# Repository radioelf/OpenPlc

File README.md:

# OpenPlc
Hardware for OpenPLC with raspberry PI Z and Mod. software OpenPlc

# Original code:
https://github.com/thiagoralves/OpenPLC_v3

Creative Commons License Disclaimer

UNLESS OTHERWISE MUTUALLY AGREED TO BY THE PARTIES IN WRITING, LICENSOR OFFERS THE WORK AS-IS AND MAKES NO REPRESENTATIONS OR WARRANTIES OF ANY KIND CONCERNING THE WORK, EXPRESS, IMPLIED, STATUTORY OR OTHERWISE, INCLUDING, WITHOUT LIMITATION, WARRANTIES OF TITLE, MERCHANTIBILITY, FITNESS FOR A PARTICULAR PURPOSE, NONINFRINGEMENT, OR THE ABSENCE OF LATENT OR OTHER DEFECTS, ACCURACY, OR THE PRESENCE OF ABSENCE OF ERRORS, WHETHER OR NOT DISCOVERABLE. SOME JURISDICTIONS DO NOT ALLOW THE EXCLUSION OF IMPLIED WARRANTIES, SO SUCH EXCLUSION MAY NOT APPLY TO YOU. EXCEPT TO THE EXTENT REQUIRED BY APPLICABLE LAW, IN NO EVENT WILL LICENSOR BE LIABLE TO YOU ON ANY LEGAL THEORY FOR ANY SPECIAL, INCIDENTAL, CONSEQUENTIAL, PUNITIVE OR EXEMPLARY DAMAGES ARISING OUT OF THIS LICENSE OR THE USE OF THE WORK, EVEN IF LICENSOR HAS BEEN ADVISED OF THE POSSIBILITY OF SUCH DAMAGES.

http://creativecommons.org/licenses/by-sa/3.0/

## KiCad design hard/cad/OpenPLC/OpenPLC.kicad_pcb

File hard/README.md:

Diseño de PCBs con Kicad para OpenPlc usando como CPU una Raspberry Pi Z (int-out) y Arduino Nano para las PBCs 
de entradas/salidas analógicas

Creative Commons License Disclaimer

UNLESS OTHERWISE MUTUALLY AGREED TO BY THE PARTIES IN WRITING, LICENSOR OFFERS THE WORK AS-IS AND MAKES NO REPRESENTATIONS OR
WARRANTIES OF ANY KIND CONCERNING THE WORK, EXPRESS, IMPLIED, STATUTORY OR OTHERWISE, INCLUDING, WITHOUT LIMITATION, 
WARRANTIES OF TITLE, MERCHANTIBILITY, FITNESS FOR A PARTICULAR PURPOSE, NONINFRINGEMENT, OR THE ABSENCE OF LATENT OR 
OTHER DEFECTS, ACCURACY, OR THE PRESENCE OF ABSENCE OF ERRORS, WHETHER OR NOT DISCOVERABLE. SOME JURISDICTIONS DO NOT 
ALLOW THE EXCLUSION OF IMPLIED WARRANTIES, SO SUCH EXCLUSION MAY NOT APPLY TO YOU. EXCEPT TO THE EXTENT REQUIRED BY 
APPLICABLE LAW, IN NO EVENT WILL LICENSOR BE LIABLE TO YOU ON ANY LEGAL THEORY FOR ANY SPECIAL, INCIDENTAL, CONSEQUENTIAL,
PUNITIVE OR EXEMPLARY DAMAGES ARISING OUT OF THIS LICENSE OR THE USE OF THE WORK, EVEN IF LICENSOR HAS BEEN ADVISED OF 
THE POSSIBILITY OF SUCH DAMAGES.

http://creativecommons.org/licenses/by-sa/3.0/

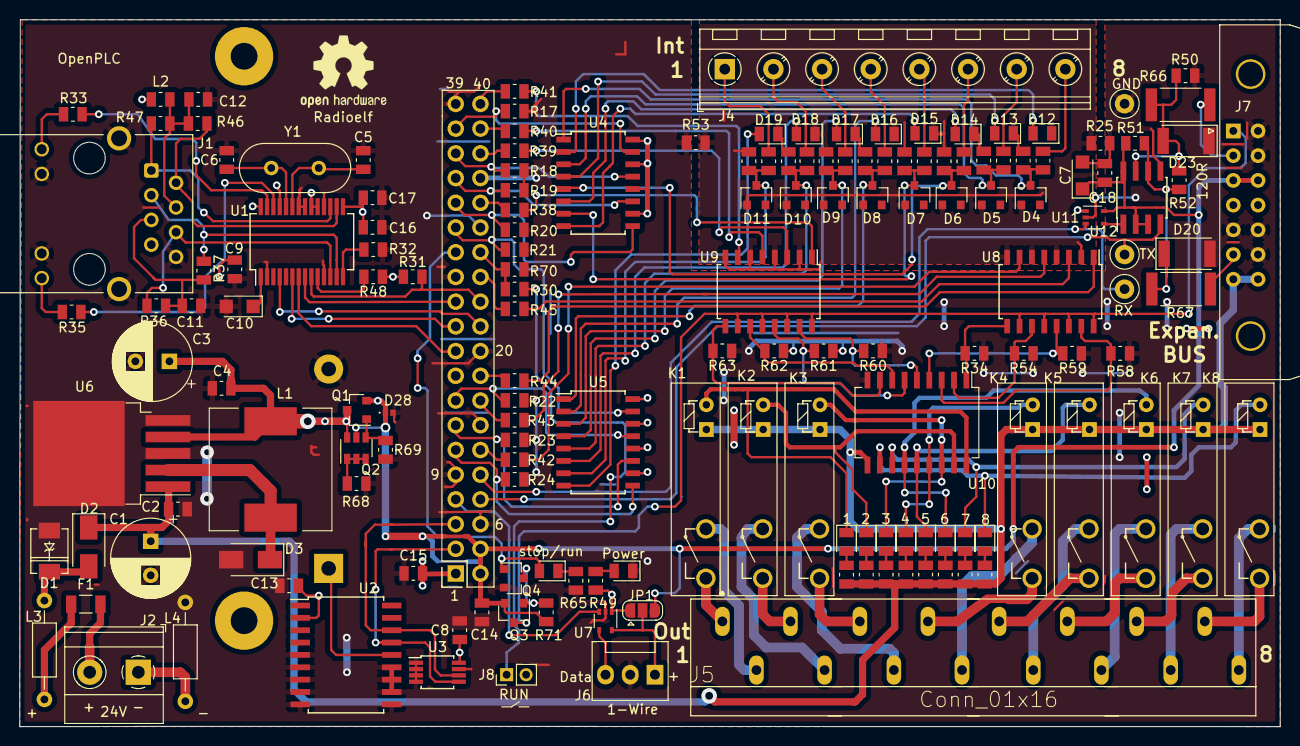
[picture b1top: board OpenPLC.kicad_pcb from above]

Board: 2 copper layers, 129.5 x 72.6 mm, 165 parts (1 on the bottom side), 141 nets.

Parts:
BT1: Battery_Cell; BatteryHolder_Keystone_103_1x20mm
C1: 100uF 50V; CP_Radial_D8.0mm_P3.50mm
C2, C4, C8, C9, C13, C14, C15, C16, C17, C18: 100nF; C_0805_2012Metric
C3: 1000uF; CP_Radial_D8.0mm_P3.50mm
C5, C6: 18pF; C_0805_2012Metric
C7, C10: 10uF; CP_EIA-3216-10_Kemet-I
C11, C12: 10nF; C_0805_2012Metric
D1: SMBJ36A; DO-214AA
D2: STPS1L30A; D_SMA
D3: SS34; D_SMA
D4, D5, D6, D7, D8, D9, D10, D11: RGF1B; D_SOT-23_ANK
D12, D13, D14, D15, D16, D17, D18, D19, D21, D24, D25, D26, D27, D29, D30, D31: LED; LED_0805_2012Metric
D20, D23: 6V8C; D_2010_5025Metric
D22: stop/run; LED_0805_2012Metric
D28: PESD0402-140; D_0402_1005Metric
D32: Power; LED_0805_2012Metric
F1: PPTC- 250mA; Fuse_1206_3216Metric
J1: RJ45-TRANSFO_HR911105A; RJ45_Hanrun_HR911105A
J2: Conn_01x02; TerminalBlock_Phoenix_MKDS-1,5-2_1x02_P5.00mm_Horizontal
J3: Raspberry_Pi_2_3; Raspberry_Pi_Zero_invert
J4: Conn_01x08; TerminalBlock_RND_205-00051_1x08_P5.00mm_Horizontal
J5: Conn_01x16; WAGO_250-204-16
J6: 1-Wire; FanPinHeader_1x03_P2.54mm_Vertical
J7: Conn_02x07_Odd_Even; IDC-Header_2x07_P2.54mm_Horizontal_Lock
J8: On-Off RUN; PinHeader_1x02_P2.00mm_Vertical
JP1: 3.3v-5v; SolderJumper-3_P1.3mm_Open_RoundedPad1.0x1.5mm
K1, K2, K3, K4, K5, K6, K7, K8: APA331; Relay_apan3124
L1: 47uH; L_12x12mm_H6mm
L2: 10uH; L_0805_2012Metric
L3, L4: 10uH; L_Axial_L5.3mm_D2.2mm_P10.16mm_Horizontal_Vishay_IM-1
LOGO1: Logo_Open_Hardware_Large; OSHW-Logo2_9.8x8mm_SilkScreen
Q1, Q3: DMG2305; SOT-23
Q2: DMMT5401; SOT-23-6
Q4: BC847; SOT-23
R1, R2, R3, R4, R5, R6, R7, R8, R26, R27, R28, R29, R55, R56, R57, R64: 4k7; R_0805_2012Metric
R9, R10, R11, R12, R13, R14, R15, R16, R31, R34, R48, R54, R58, R59, R60, R61, R62, R63, R70: 10k; R_0805_2012Metric
R17, R18, R19, R20, R21, R22, R23, R24: 5k1; R_0805_2012Metric
R25, R53: 0R; R_0805_2012Metric
R30, R33, R35, R38, R39, R40, R41, R42, R43, R44, R45, R49, R65: 1k; R_0805_2012Metric
R32: 2k7; R_0805_2012Metric
R36, R37, R46, R47: 50R; R_0805_2012Metric
R50, R51: 4k2; R_0805_2012Metric
R52: 120R; R_0805_2012Metric
R66, R67: 100R; R_2512_6332Metric
R68, R69, R71: 47K; R_0805_2012Metric
TP1: RX; TestPoint_Loop_D1.80mm_Drill1.0mm_Beaded
TP2: TX; TestPoint_Loop_D1.80mm_Drill1.0mm_Beaded
TP3: GND; TestPoint_Loop_D1.80mm_Drill1.0mm_Beaded
U1: ENC28J60x-SS; SSOP-28_5.3x10.2mm_P0.65mm
U2: DS3231MZ; SOIC-18W_7.5x11.6mm_P1.27mm
U3: 24LC32; MSOP-8_3x3mm_P0.65mm
U4, U5, U8, U9: TLP281-4; SOIC-16W_5.3x10.2mm_P1.27mm
U6: LM2596S-5; TO-263-5_TabPin3
U7, U11: MAX3370; SOT-353_SC-70-5
U10: ULN2803A; SOP-18_7.0x12.5mm_P1.27mm
U12: MAX13487; PowerIntegrations_SO-8
Y1: 25Mhz; Crystal_HC49-4H_Vertical

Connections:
+3V3: C8.2, C9.2, C13.1, C15.2, C16.1, C17.2, J3.1, J3.17, J7.7, J7.8, J8.2, JP1.1, L2.1, R31.2, R48.1, R49.1, U1.15, U1.19, U1.20, U1.25, U1.28, U2.2, U3.8, U4.10, U4.12, U4.14, U4.16, U5.10, U5.12, U5.14, U5.16, U7.1, U11.1
+5V: C7.1, C14.2, C18.2, D28.1, J3.2, J3.4, J7.5, J7.6, JP1.3, Q1.2, Q2.5, Q3.2, R51.2, R71.1, U11.5, U12.2, U12.3, U12.8
+24V: C1.1, C2.1, D2.1, J7.13, J7.14, K1.3, K2.3, K3.3, K4.3, K5.3, K6.3, K7.3, K8.3, R26.1, R27.1, R28.1, R29.1, R55.1, R56.1, R57.1, R64.1, U6.1, U10.10
/%IX0.0: J3.11, R24.1, U5.9
/%IX0.1: J3.13, R23.1, U5.11
/%IX0.2: J3.15, R22.1, U5.13
/%IX0.3: J3.29, R21.1, U5.15
/%IX0.4: J3.31, R20.1, U4.9
/%IX0.5: J3.33, R19.1, U4.11
/%IX0.6: J3.35, R18.1, U4.13
/%IX0.7: J3.37, R17.1, U4.15
/%QV0.7: J3.40, R41.2
/%QX0.0: J3.12, R42.2
/%QX0.1: J3.16, R43.2
/%QX0.2: J3.18, R44.2
/%QX0.3: J3.26, R45.2
/%QX0.4: J3.32, R38.2
/%QX0.5: J3.36, R39.2
/%QX0.6: J3.38, R40.2
/Bus/A-RS485: J7.11, R67.1
/Bus/B-RS485: J7.3, R66.1
/CLK: J3.23, U1.8
/EtherCAT/Reset: R48.2, U1.10
/MISO: J3.21, U1.6
/MOSI: J3.19, U1.7
/RPI-Zero/1-Wire: J3.7, U7.3
/RPI-Zero/LED: D22.2, J3.27, Q4.1
/RPI-Zero/On-Off: J8.1, R30.1
/RPI-Zero/RUN: J3.28, R30.2, R70.2
/RUN-STOP: J7.1, Q3.3, U8.10, U8.12, U8.14, U8.16, U9.10, U9.12, U9.14, U9.16
/RXD: J3.10, TP1.1, U11.3
/SDA: J3.3, U2.15, U3.5
/SDL: J3.5, U2.16, U3.6
/TXD: J3.8, TP2.1, U12.4
/outputs/Out1A: J5.1, K1.2
/outputs/Out1B: J5.2, K1.1
/outputs/Out2A: J5.3, K2.2
/outputs/Out2B: J5.4, K2.1
/outputs/Out3A: J5.5, K3.2
/outputs/Out3B: J5.6, K3.1
/outputs/Out4A: J5.7, K4.2
/outputs/Out4B: J5.8, K4.1
/outputs/Out5A: J5.9, K5.2
/outputs/Out5B: J5.10, K5.1
/outputs/Out6A: J5.11, K6.2
/outputs/Out6B: J5.12, K6.1
/outputs/Out7A: J5.13, K7.2
/outputs/Out7B: J5.14, K7.1
/outputs/Out8A: J5.15, K8.2
/outputs/Out8B: J5.16, K8.1
/~CS: J3.24, R31.1, U1.9
/~INT: J3.22, U1.4
GND: BT1.2, C1.2, C2.2, C3.2, C4.2, C5.2, C6.1, C7.2, C8.1, C9.1, C10.2, C11.1, C12.1, C13.2, C14.1, C15.1, C16.2, C17.1, C18.1, D1.2, D3.2, D20.2, D23.1, D28.2, D32.1, J1.8, J1.10, J1.11, J1.SH, J3.6, J3.9, J3.14, J3.20, J3.25, J3.30, J3.34, J3.39, J6.2, J7.2, J7.4, J7.9, J7.10, J7.12, L4.1, Q4.2, R17.2, R18.2, R19.2, R20.2, R21.2, R22.2, R23.2, R24.2, R25.1, R32.2, R34.1, R50.1, R53.1, R54.1, R58.1, R59.1, R60.1, R61.1, R62.1, R63.1, R65.2, R68.2, R69.2, R70.1, TP3.1, U1.2, U1.11, U1.18, U1.21, U1.22, U2.5, U2.6, U2.7, U2.8, U2.9, U2.10, U2.11, U2.12, U2.13, U3.1, U3.2, U3.3, U3.4, U3.7, U6.3, U6.5, U7.2, U10.9, U11.2, U12.5
GNDREF: D4.2, D5.2, D6.2, D7.2, D8.2, D9.2, D10.2, D11.2, D12.1, D13.1, D14.1, D15.1, D16.1, D17.1, D18.1, D19.1, R9.2, R10.2, R11.2, R12.2, R13.2, R14.2, R15.2, R16.2, R25.2, R53.2, U8.2, U8.4, U8.6, U8.8, U9.2, U9.4, U9.6, U9.8
unnamed: BT1.1, U2.14
unnamed: C3.1, C4.1, L1.2, Q1.3, Q2.6, U6.4
unnamed: C5.1, U1.23, Y1.1
unnamed: C6.2, U1.24, Y1.2
unnamed: C10.1, U1.1
unnamed: C11.2, J1.5, R36.1, R37.1
unnamed: C12.2, J1.4, L2.2, R46.1, R47.1
unnamed: D1.1, D2.2, L3.2
unnamed: D3.1, L1.1, U6.2
unnamed: D4.1, R1.1, R11.1, U4.1
unnamed: D5.1, R2.1, R12.1, U4.3
unnamed: D6.1, R3.1, R13.1, U4.5
unnamed: D7.1, R4.1, R14.1, U4.7
unnamed: D8.1, R5.1, R15.1, U5.1
unnamed: D9.1, R6.1, R16.1, U5.3
unnamed: D10.1, R7.1, R9.1, U5.5
unnamed: D11.1, R8.1, R10.1, U5.7
unnamed: D12.2, U4.2
unnamed: D13.2, U4.4
unnamed: D14.2, U4.6
unnamed: D15.2, U4.8
unnamed: D16.2, U5.2
unnamed: D17.2, U5.4
unnamed: D18.2, U5.6
unnamed: D19.2, U5.8
unnamed: D20.1, R51.1, R52.1, R67.2, U12.6
unnamed: D21.1, K1.4, U10.18
unnamed: D21.2, R64.2
unnamed: D22.1, R65.1
unnamed: D23.2, R50.2, R52.2, R66.2, U12.7
unnamed: D24.1, K6.4, U10.13
unnamed: D24.2, R26.2
unnamed: D25.1, K5.4, U10.14
unnamed: D25.2, R27.2
unnamed: D26.1, K8.4, U10.11
unnamed: D26.2, R28.2
unnamed: D27.1, K7.4, U10.12
unnamed: D27.2, R29.2
unnamed: D29.1, K2.4, U10.17
unnamed: D29.2, R55.2
unnamed: D30.1, K3.4, U10.16
unnamed: D30.2, R56.2
unnamed: D31.1, K4.4, U10.15
unnamed: D31.2, R57.2
unnamed: D32.2, R49.2
unnamed: F1.1, L3.1
unnamed: F1.2, J2.2
unnamed: J1.1, R47.2, U1.17
unnamed: J1.2, R46.2, U1.16
unnamed: J1.3, R37.2, U1.13
unnamed: J1.6, R36.2, U1.12
unnamed: J1.9, R33.1
unnamed: J1.12, R35.1
unnamed: J2.1, L4.2
unnamed: J4.1, R8.2
unnamed: J4.2, R7.2
unnamed: J4.3, R6.2
unnamed: J4.4, R5.2
unnamed: J4.5, R4.2
unnamed: J4.6, R3.2
unnamed: J4.7, R2.2
unnamed: J4.8, R1.2
unnamed: J6.1, JP1.2, U7.5
unnamed: J6.3, U7.4
unnamed: Q1.1, Q2.4, R69.1
unnamed: Q2.1, Q2.2, Q2.3, R68.1
unnamed: Q3.1, Q4.3, R71.2
unnamed: R32.1, U1.14
unnamed: R33.2, U1.27
unnamed: R34.2, U8.9, U10.1
unnamed: R35.2, U1.26
unnamed: R38.1, U9.1
unnamed: R39.1, U9.3
unnamed: R40.1, U9.5
unnamed: R41.1, U9.7
unnamed: R42.1, U8.7
unnamed: R43.1, U8.5
unnamed: R44.1, U8.1
unnamed: R45.1, U8.3
unnamed: R54.2, U8.11, U10.2
unnamed: R58.2, U8.15, U10.3
unnamed: R59.2, U8.13, U10.4
unnamed: R60.2, U9.15, U10.5
unnamed: R61.2, U9.13, U10.6
unnamed: R62.2, U9.11, U10.7
unnamed: R63.2, U9.9, U10.8
unnamed: U11.4, U12.1

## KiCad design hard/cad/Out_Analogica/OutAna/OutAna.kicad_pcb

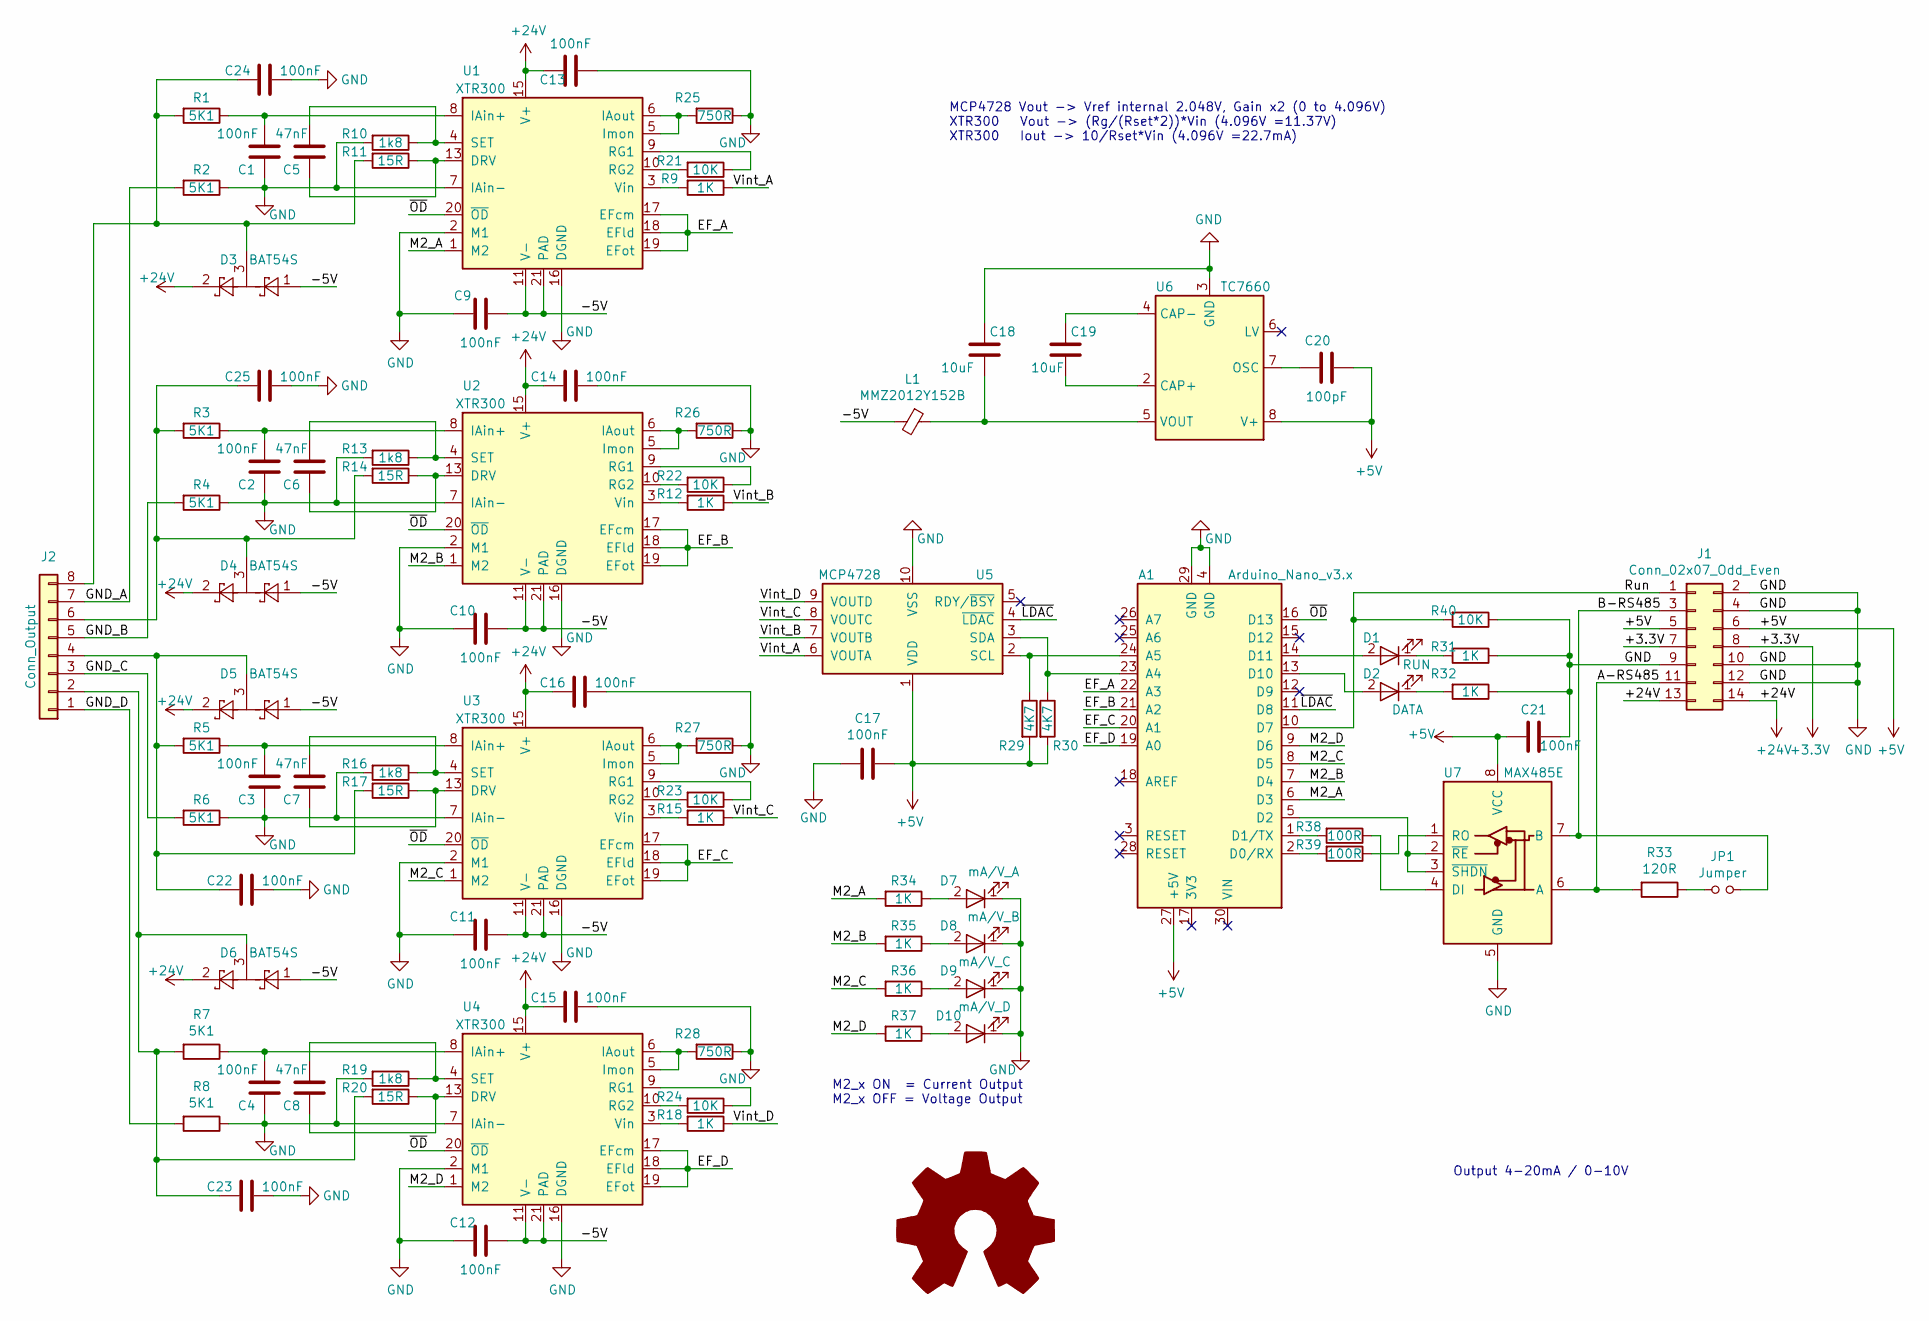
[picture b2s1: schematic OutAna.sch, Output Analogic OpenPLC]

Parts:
A1: Arduino_Nano_v3.x; Arduino_Nano
C1, C2, C3, C4, C9, C10, C11, C12, C13, C14, C15, C16, C17, C21, C22, C23, C24, C25: 100nF; C_0805_2012Metric
C5, C6, C7, C8: 47nF; C_0805_2012Metric
C18, C19: 10uF; C_0805_2012Metric
C20: 100pF; C_0805_2012Metric
D1: RUN; LED_0603_1608Metric
D2: DATA; LED_0603_1608Metric
D3, D4, D5, D6: BAT54S; SOT-23
D7: mA/V_A; LED_0603_1608Metric
D8: mA/V_B; LED_0603_1608Metric
D9: mA/V_C; LED_0603_1608Metric
D10: mA/V_D; LED_0603_1608Metric
J1: Conn_02x07_Odd_Even; IDC-Header_2x07_P2.54mm_Vertical
J2: Conn_Output; PhoenixContact_MCV_1,5_8-G-3.5_1x08_P3.50mm_Vertical
JP1: Jumper; SolderJumper-2_P1.3mm_Open_RoundedPad1.0x1.5mm
L1: MMZ2012Y152B; L_0805_2012Metric
LOGO1: Logo_Open_Hardware_Large; OSHW-Logo2_9.8x8mm_SilkScreen
R1, R2, R3, R4, R5, R6, R7, R8: 5K1; R_0805_2012Metric
R9, R12, R15, R18, R31, R32, R34, R35, R36, R37: 1K; R_0805_2012Metric
R10, R13, R16, R19: 1k8; R_0805_2012Metric
R11, R14, R17, R20: 15R; R_0805_2012Metric
R21, R22, R23, R24, R40: 10K; R_0805_2012Metric
R25, R26, R27, R28: 750R; R_0805_2012Metric
R29, R30: 4K7; R_0805_2012Metric
R33: 120R; R_0805_2012Metric
R38, R39: 100R; R_0805_2012Metric
U1, U2, U3, U4: XTR300; QFN-20-1EP_5x5mm_P0.65mm_EP3.35x3.35mm
U5: MCP4728; MSOP-10_3x3mm_P0.5mm
U6: TC7660; SOIC-8_3.9x4.9mm_P1.27mm
U7: MAX485E; PowerIntegrations_SO-8

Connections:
+3V3: J1.7, J1.8
+5V: A1.27 (+5V), C17.1, C20.2, C21.2, J1.5, J1.6, R29.2, R30.2, U5.1 (VDD), U6.8 (V+), U7.8 (VCC)
+24V: C13.1, C14.1, C15.1, C16.1, D3.2, D4.2, D5.2, D6.2, J1.13, J1.14, U1.15 (V+), U2.15 (V+), U3.15 (V+), U4.15 (V+)
/-5V: C9.2, C10.2, C11.2, C12.2, D3.1, D4.1, D5.1, D6.1, L1.2, U1.11 (V-), U1.21 (PAD), U2.11 (V-), U2.21 (PAD), U3.11 (V-), U3.21 (PAD), U4.11 (V-), U4.21 (PAD)
/A-RS485: J1.11, R33.2, U7.6 (A)
/B-RS485: J1.3, JP1.2, U7.7 (B)
/EF_A: A1.22 (A3), U1.17 (EFcm), U1.18 (EFld), U1.19 (EFot)
/EF_B: A1.21 (A2), U2.17 (EFcm), U2.18 (EFld), U2.19 (EFot)
/EF_C: A1.20 (A1), U3.17 (EFcm), U3.18 (EFld), U3.19 (EFot)
/EF_D: A1.19 (A0), U4.17 (EFcm), U4.18 (EFld), U4.19 (EFot)
/GND_A: J2.7, R2.2
/GND_B: J2.5, R4.2
/GND_C: J2.3, R6.2
/GND_D: J2.1, R8.2
/M2_A: A1.6 (D3), R34.2, U1.1 (M2)
/M2_B: A1.7 (D4), R35.2, U2.1 (M2)
/M2_C: A1.8 (D5), R36.2, U3.1 (M2)
/M2_D: A1.9 (D6), R37.2, U4.1 (M2)
/Run: A1.10 (D7), J1.1, R40.2
/Vint_A: R9.1, U5.6 (VOUTA)
/Vint_B: R12.1, U5.7 (VOUTB)
/Vint_C: R15.1, U5.8 (VOUTC)
/Vint_D: R18.1, U5.9 (VOUTD)
/~LDAC: A1.11 (D8), U5.4 (~LDAC)
/~OD: A1.16 (D13), U1.20 (~OD), U2.20 (~OD), U3.20 (~OD), U4.20 (~OD)
GND: A1.4 (GND), A1.29 (GND), C1.2, C2.2, C3.2, C4.2, C9.1, C10.1, C11.1, C12.1, C13.2, C14.2, C15.2, C16.2, C17.2, C18.1, C21.1, C22.2, C23.2, C24.2, C25.2, D7.1 (K), D8.1 (K), D9.1 (K), D10.1 (K), J1.2, J1.4, J1.9, J1.10, J1.12, R2.1, R4.1, R6.1, R8.1, R10.2, R13.2, R16.2, R19.2, R25.1, R26.1, R27.1, R28.1, R31.1, R32.1, R40.1, U1.2 (M1), U1.7 (IAin-), U1.16 (DGND), U2.2 (M1), U2.7 (IAin-), U2.16 (DGND), U3.2 (M1), U3.7 (IAin-), U3.16 (DGND), U4.2 (M1), U4.7 (IAin-), U4.16 (DGND), U5.10 (VSS), U6.3 (GND), U7.5 (GND)
unnamed: A1.1 (D1/TX), R38.2
unnamed: A1.2 (D0/RX), R39.2
unnamed: A1.5 (D2), U7.2 (~RE), U7.3 (~SHDN)
unnamed: A1.13 (D10), D2.2 (A)
unnamed: A1.14 (D11), D1.2 (A)
unnamed: A1.23 (A4), R30.1, U5.3 (SDA)
unnamed: A1.24 (A5), R29.1, U5.2 (SCL)
unnamed: C1.1, R1.1, U1.8 (IAin+)
unnamed: C2.1, R3.1, U2.8 (IAin+)
unnamed: C3.1, R5.1, U3.8 (IAin+)
unnamed: C4.1, R7.1, U4.8 (IAin+)
unnamed: C5.1, R10.1, U1.4 (SET)
unnamed: C5.2, R11.1, U1.13 (DRV)
unnamed: C6.1, R13.1, U2.4 (SET)
unnamed: C6.2, R14.1, U2.13 (DRV)
unnamed: C7.1, R16.1, U3.4 (SET)
unnamed: C7.2, R17.1, U3.13 (DRV)
unnamed: C8.1, R19.1, U4.4 (SET)
unnamed: C8.2, R20.1, U4.13 (DRV)
unnamed: C18.2, L1.1, U6.5 (VOUT)
unnamed: C19.1, U6.4 (CAP-)
unnamed: C19.2, U6.2 (CAP+)
unnamed: C20.1, U6.7 (OSC)
unnamed: C22.1, D5.3, J2.4, R5.2, R17.2
unnamed: C23.1, D6.3, J2.2, R7.2, R20.2
unnamed: C24.1, D3.3, J2.8, R1.2, R11.2
unnamed: C25.1, D4.3, J2.6, R3.2, R14.2
unnamed: D1.1 (K), R31.2
unnamed: D2.1 (K), R32.2
unnamed: D7.2 (A), R34.1
unnamed: D8.2 (A), R35.1
unnamed: D9.2 (A), R36.1
unnamed: D10.2 (A), R37.1
unnamed: JP1.1, R33.1
unnamed: R9.2, U1.3 (Vin)
unnamed: R12.2, U2.3 (Vin)
unnamed: R15.2, U3.3 (Vin)
unnamed: R18.2, U4.3 (Vin)
unnamed: R21.1, U1.9 (RG1)
unnamed: R21.2, U1.10 (RG2)
unnamed: R22.1, U2.9 (RG1)
unnamed: R22.2, U2.10 (RG2)
unnamed: R23.1, U3.9 (RG1)
unnamed: R23.2, U3.10 (RG2)
unnamed: R24.1, U4.9 (RG1)
unnamed: R24.2, U4.10 (RG2)
unnamed: R25.2, U1.5 (Imon), U1.6 (IAout)
unnamed: R26.2, U2.5 (Imon), U2.6 (IAout)
unnamed: R27.2, U3.5 (Imon), U3.6 (IAout)
unnamed: R28.2, U4.5 (Imon), U4.6 (IAout)
unnamed: R38.1, U7.4 (DI)
unnamed: R39.1, U7.1 (RO)

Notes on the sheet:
Output 4-20mA / 0-10V
M2_x ON = Current Output M2_x OFF = Voltage Output
MCP4728 Vout -> Vref internal 2.048V, Gain x2 (0 to 4.096V) XTR300 Vout -> (Rg/(Rset*2))*Vin (4.096V =11.37V) XTR300 Iout -> 10/Rset*Vin (4.096V =22.7mA)

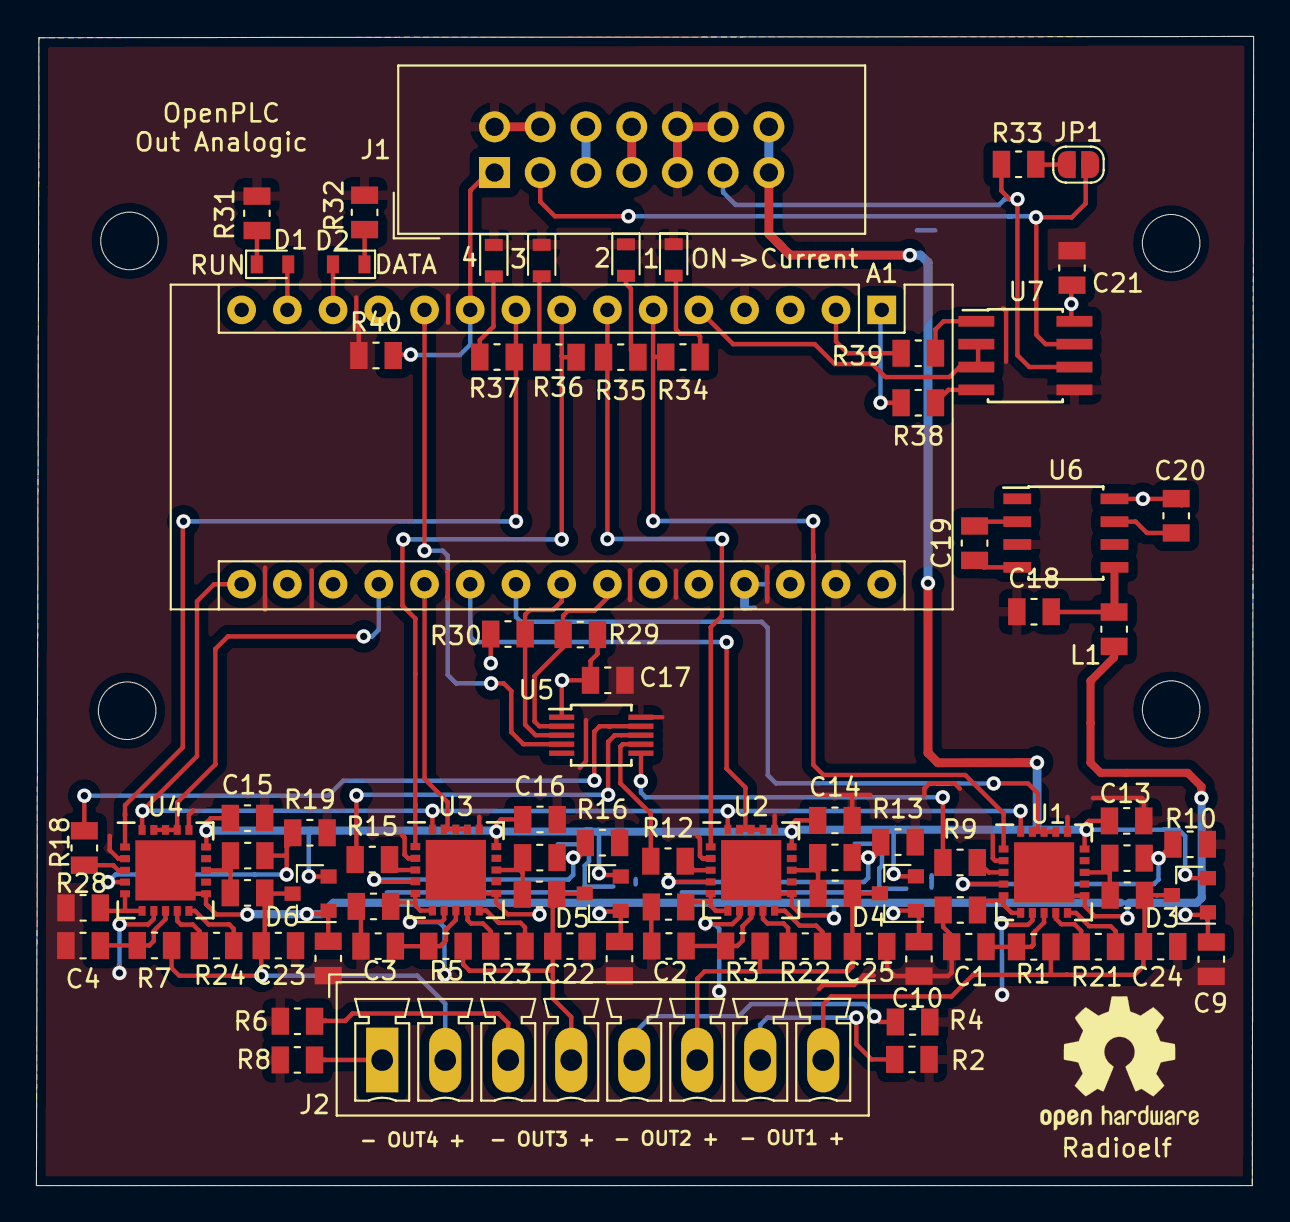
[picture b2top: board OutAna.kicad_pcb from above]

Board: 2 copper layers, 67.6 x 63.8 mm, 88 parts (0 on the bottom side), 78 nets.

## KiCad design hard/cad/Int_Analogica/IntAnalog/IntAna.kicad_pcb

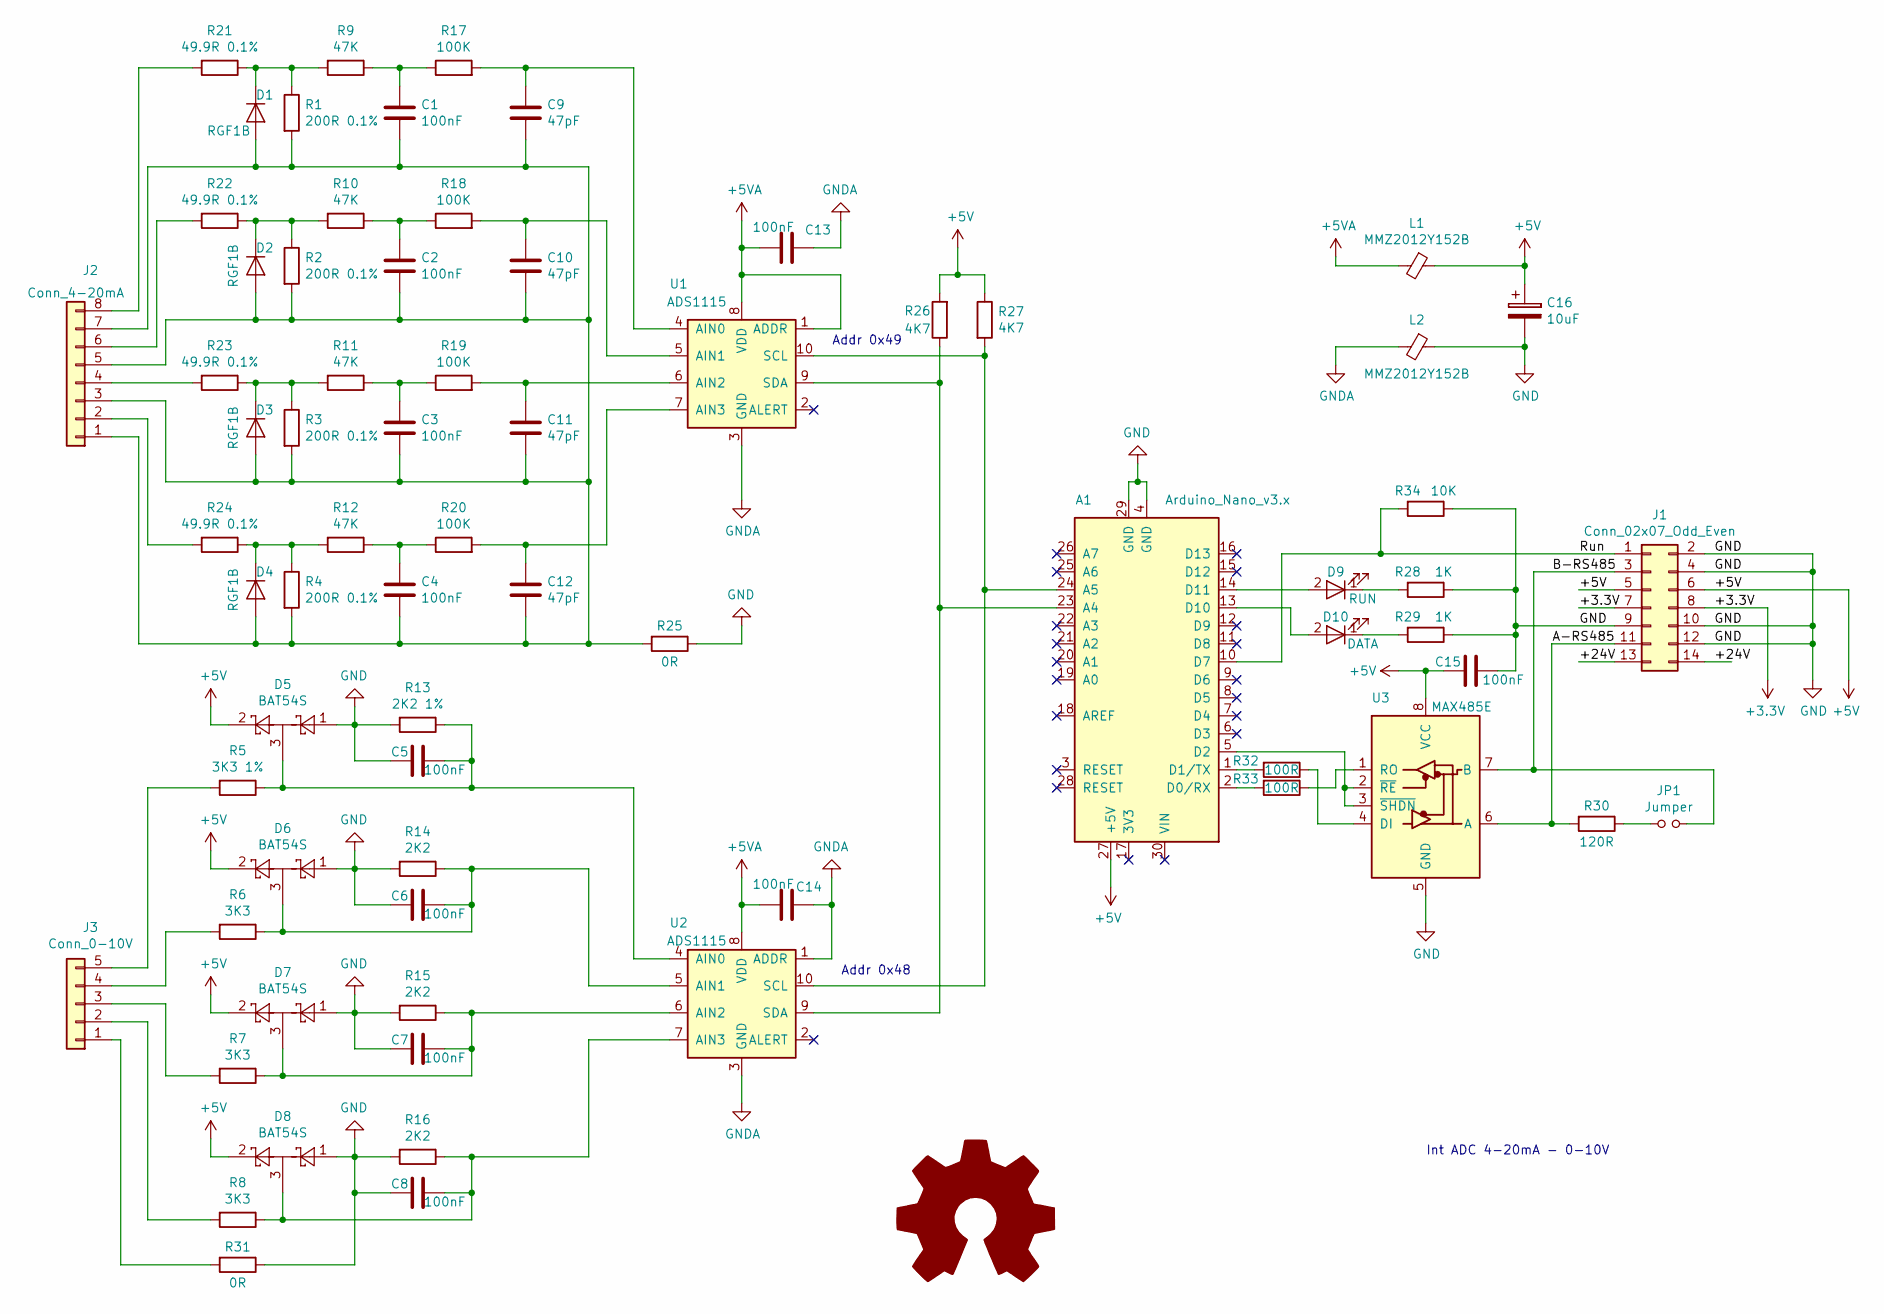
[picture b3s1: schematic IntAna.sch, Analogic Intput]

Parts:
A1: Arduino_Nano_v3.x; Arduino_Nano
C1, C2, C3, C4, C5, C6, C7, C8, C13, C14, C15: 100nF; C_0805_2012Metric
C9, C10, C11, C12: 47pF; C_0805_2012Metric
C16: 10uF; CP_EIA-6032-28_Kemet-C
D1, D2, D3, D4: RGF1B; D_SOT-23_ANK
D5, D6, D7, D8: BAT54S; SOT-23
D9: RUN; LED_0805_2012Metric
D10: DATA; LED_0805_2012Metric
J1: Conn_02x07_Odd_Even; IDC-Header_2x07_P2.54mm_Vertical
J2: Conn_4-20mA; PhoenixContact_MCV_1,5_8-G-3.5_1x08_P3.50mm_Vertical
J3: Conn_0-10V; PhoenixContact_MCV_1,5_5-G-3.5_1x05_P3.50mm_Vertical
JP1: Jumper; SolderJumper-2_P1.3mm_Open_RoundedPad1.0x1.5mm
L1, L2: MMZ2012Y152B; R_0805_2012Metric
LOGO1: Logo_Open_Hardware_Large; OSHW-Logo2_9.8x8mm_SilkScreen
R1, R2, R3, R4: 200R 0.1%; R_0805_2012Metric
R5: 3K3 1%; R_0805_2012Metric
R6, R7, R8: 3K3; R_0805_2012Metric
R9, R10, R11, R12: 47K; R_0805_2012Metric
R13: 2K2 1%; R_0805_2012Metric
R14, R15, R16: 2K2; R_0805_2012Metric
R17, R18, R19, R20: 100K; R_0805_2012Metric
R21, R22, R23, R24: 49.9R 0.1%; R_0805_2012Metric
R25, R31: 0R; R_0805_2012Metric
R26, R27: 4K7; R_0805_2012Metric
R28, R29: 1K; R_0805_2012Metric
R30: 120R; R_0805_2012Metric
R32, R33: 100R; R_0805_2012Metric
R34: 10K; R_0805_2012Metric
U1, U2: ADS1115; TSSOP-10_3x3mm_P0.5mm
U3: MAX485E; PowerIntegrations_SO-8

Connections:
+3V3: J1.7, J1.8
+5V: A1.27 (+5V), C15.1, C16.1, D5.2, D6.2, D7.2, D8.2, J1.5, J1.6, L1.1, R26.2, R27.1, U3.8 (VCC)
+5VA: C13.1, C14.1, L1.2, U1.1 (ADDR), U1.8 (VDD), U2.8 (VDD)
/+24V: J1.13, J1.14
/A-RS485: J1.11, R30.2, U3.6 (A)
/B-RS485: J1.3, JP1.2, U3.7 (B)
/Run: A1.10 (D7), J1.1, R34.2
GND: A1.4 (GND), A1.29 (GND), C5.2, C6.2, C7.2, C8.2, C15.2, C16.2, D5.1, D6.1, D7.1, D8.1, J1.2, J1.4, J1.9, J1.10, J1.12, L2.1, R13.2, R14.2, R15.2, R16.2, R25.1, R28.1, R29.1, R31.1, R34.1, U3.5 (GND)
GNDA: C13.2, C14.2, L2.2, U1.3 (GND), U2.1 (ADDR), U2.3 (GND)
unnamed: A1.1 (D1/TX), R32.2
unnamed: A1.2 (D0/RX), R33.2
unnamed: A1.5 (D2), U3.2 (~RE), U3.3 (~SHDN)
unnamed: A1.13 (D10), D10.2 (A)
unnamed: A1.14 (D11), D9.2 (A)
unnamed: A1.23 (A4), R26.1, U1.9 (SDA), U2.9 (SDA)
unnamed: A1.24 (A5), R27.2, U1.10 (SCL), U2.10 (SCL)
unnamed: C1.1, R9.1, R17.1
unnamed: C1.2, C2.2, C3.2, C4.2, C9.2, C10.2, C11.2, C12.2, D1.2 (A), D2.2 (A), D3.2 (A), D4.2 (A), J2.1, J2.3, J2.5, J2.7, R1.2, R2.2, R3.2, R4.2, R25.2
unnamed: C2.1, R10.1, R18.1
unnamed: C3.1, R11.1, R19.1
unnamed: C4.1, R12.1, R20.1
unnamed: C5.1, D5.3, R5.1, R13.1, U2.4 (AIN0)
unnamed: C6.1, D6.3, R6.1, R14.1, U2.5 (AIN1)
unnamed: C7.1, D7.3, R7.1, R15.1, U2.6 (AIN2)
unnamed: C8.1, D8.3, R8.1, R16.1, U2.7 (AIN3)
unnamed: C9.1, R17.2, U1.4 (AIN0)
unnamed: C10.1, R18.2, U1.5 (AIN1)
unnamed: C11.1, R19.2, U1.6 (AIN2)
unnamed: C12.1, R20.2, U1.7 (AIN3)
unnamed: D1.1 (K), R1.1, R9.2, R21.1
unnamed: D2.1 (K), R2.1, R10.2, R22.1
unnamed: D3.1 (K), R3.1, R11.2, R23.1
unnamed: D4.1 (K), R4.1, R12.2, R24.1
unnamed: D9.1 (K), R28.2
unnamed: D10.1 (K), R29.2
unnamed: J2.2, R24.2
unnamed: J2.4, R23.2
unnamed: J2.6, R22.2
unnamed: J2.8, R21.2
unnamed: J3.1, R31.2
unnamed: J3.2, R8.2
unnamed: J3.3, R7.2
unnamed: J3.4, R6.2
unnamed: J3.5, R5.2
unnamed: JP1.1, R30.1
unnamed: R32.1, U3.4 (DI)
unnamed: R33.1, U3.1 (RO)

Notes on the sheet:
Int ADC 4-20mA - 0-10V
Addr 0x49
Addr 0x48

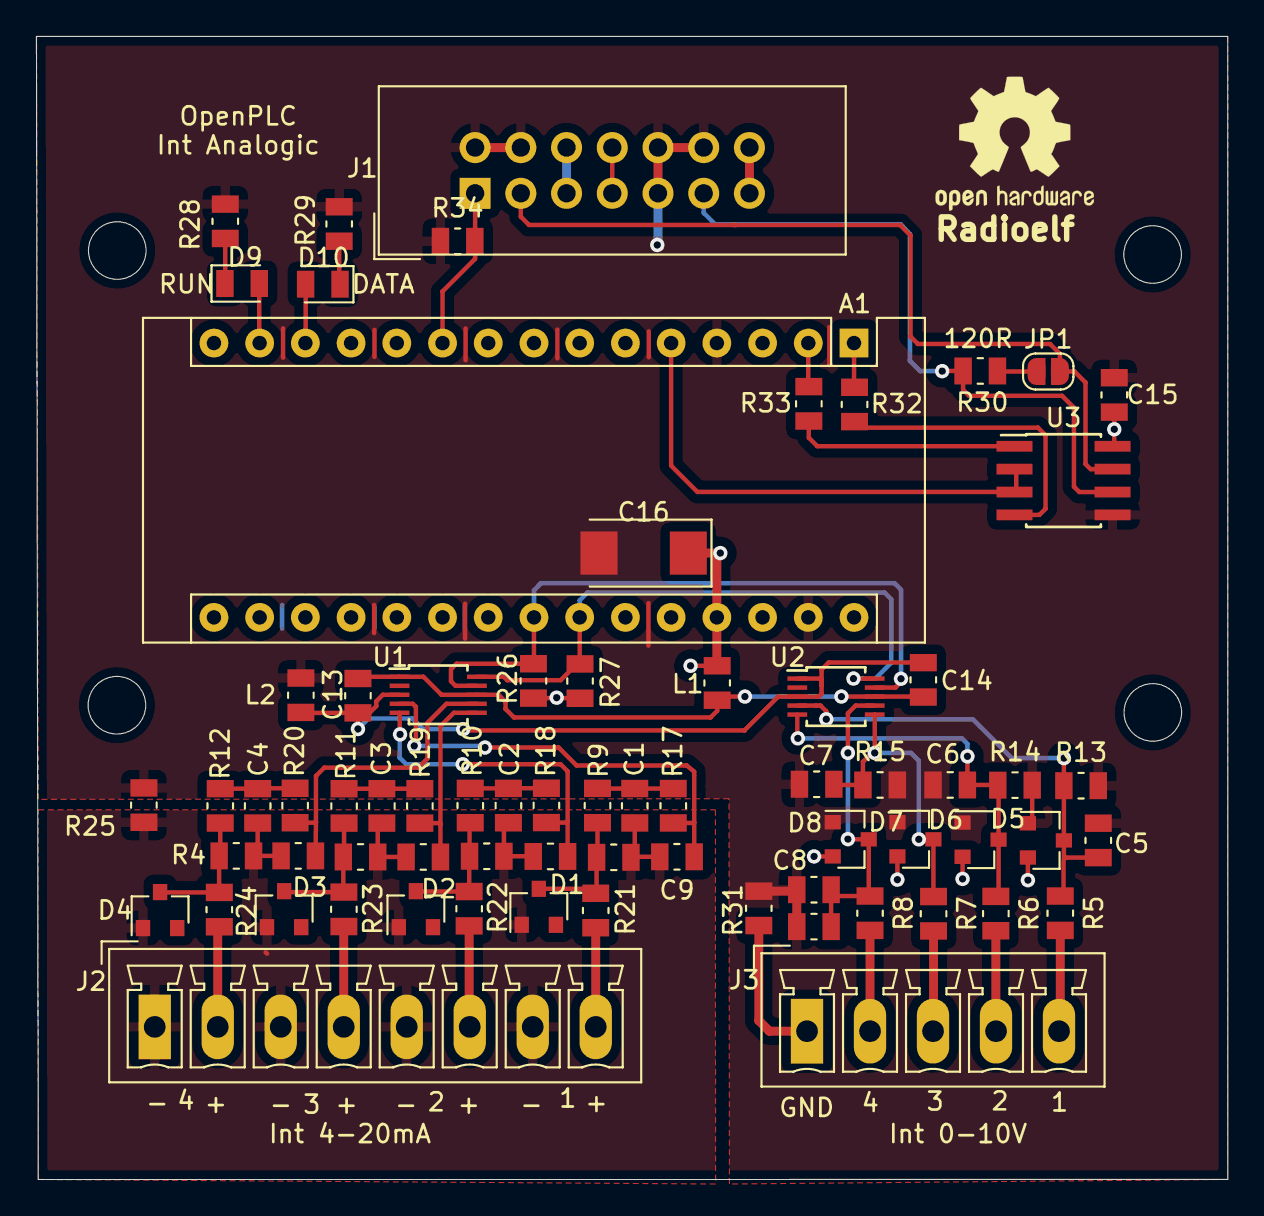
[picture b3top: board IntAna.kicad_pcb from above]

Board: 2 copper layers, 66.2 x 63.5 mm, 71 parts (0 on the bottom side), 47 nets.

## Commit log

2019-12-03 Rename sof/OpenPLC_v3/README.md to sof/ OpenPLC_v3/README_original.md
2023-05-01 Bump flask from 1.0.2 to 2.3.2 in /sof/OpenPLC_v3
    Bumps [flask](https://github.com/pallets/flask) from 1.0.2 to 2.3.2.
    - [Release notes](https://github.com/pallets/flask/releases)
    - [Changelog](https://github.com/pallets/flask/blob/main/CHANGES.rst)
    - [Commits](https://github.com/pallets/flask/compare/1.0.2...2.3.2)
    ---
    updated-dependencies:
